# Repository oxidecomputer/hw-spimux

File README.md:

# hw-spimux

PMOD Quad SPI flash mux debug board
Breaks out the Gimletlet QSPI port to a MT25QU256ABA8E12 Flash memory IC.

# Model Change Notices
We use Model Change Notices (MCNs) to track rework made in between CAD updates 
andboard spins.
These are preserved in this repo for historical and reference reasons even
after the CAD has been updated.

# Status
The CAD represents what was built without the MCN(s) applied.

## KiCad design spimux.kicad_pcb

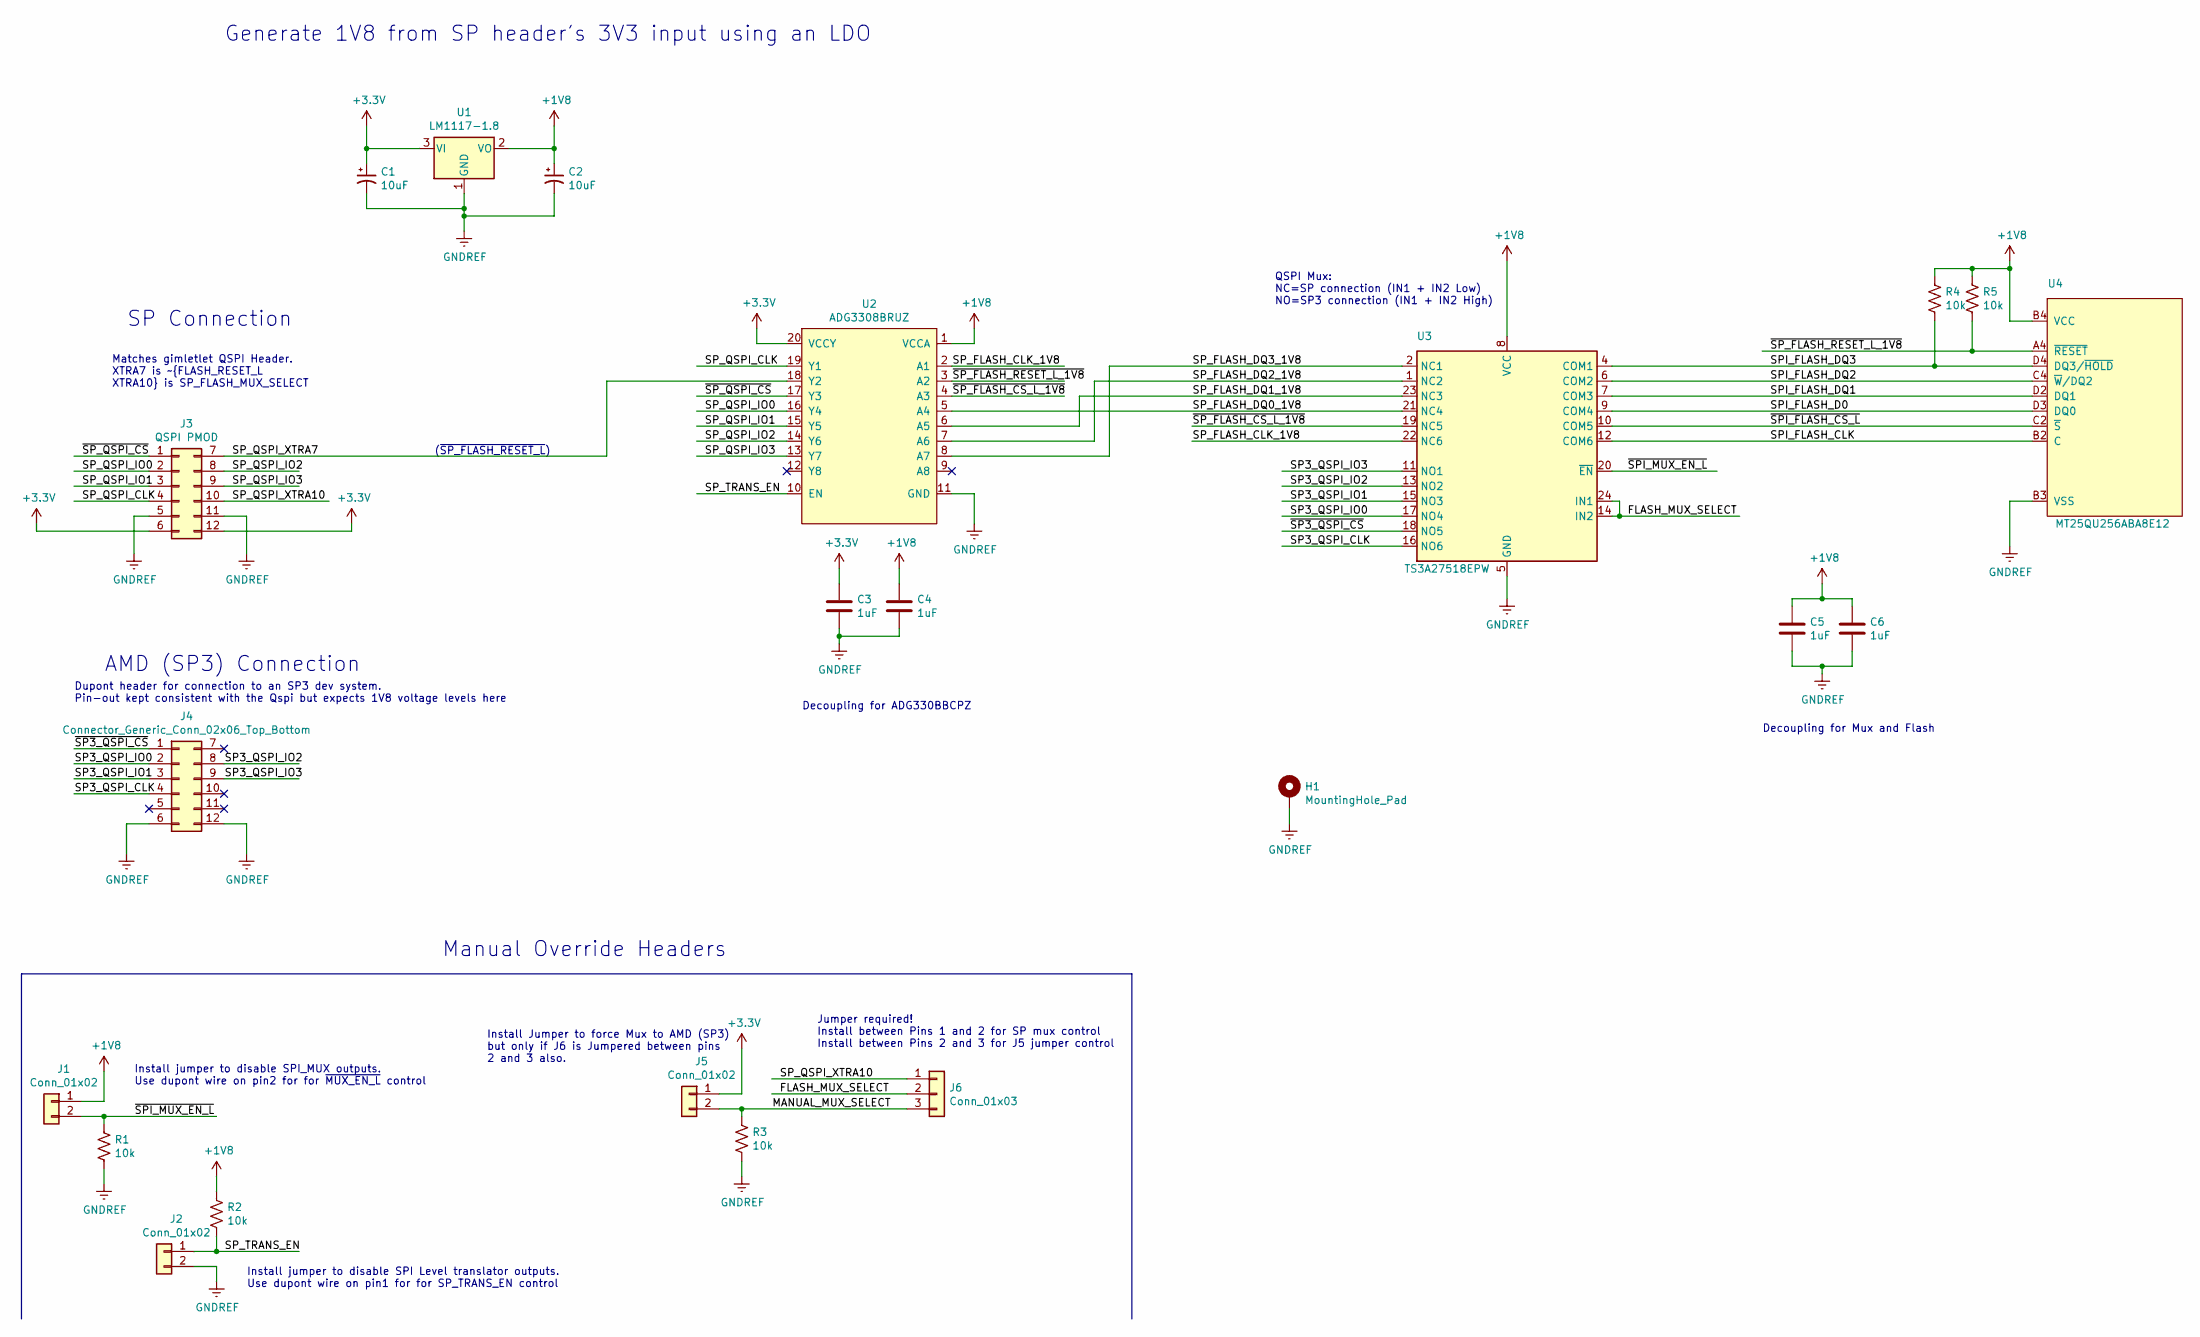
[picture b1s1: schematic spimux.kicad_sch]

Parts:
C1, C2: 10uF; CP_Elec_5x5.3; MPN EDK106M050A9DAA
C3, C4, C5, C6: 1uF; C_0402_1005Metric
H1: MountingHole_Pad; MountingHole_3.2mm_M3_Pad
J1, J2, J5: Conn_01x02; PinHeader_1x02_P2.54mm_Vertical; MPN PRPC024SAAN-RC
J3: QSPI PMOD; PMOD_12pin_peripheral_horizontal
J4: Connector_Generic_Conn_02x06_Top_Bottom; PinHeader_2x06_P2.54mm_Vertical
J6: Conn_01x03; PinHeader_1x03_P2.54mm_Vertical; MPN PRPC024SAAN-RC
R1, R2, R3, R4, R5: 10k; R_0402_1005Metric
U1: LM1117-1.8; SOT-223; MPN LM1117MPX-18NOPB
U2: ADG3308BRUZ; TSSOP-20_4.4x6.5mm_P0.65mm
U3: TS3A27518EPW; TSSOP-24_4.4x7.8mm_P0.65mm; MPN TS3A27518EPWR
U4: MT25QU256ABA8E12; BGA-25_5x5_6.0x8.0mm

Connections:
+1V8: C2.1, C4.1, C5.1, C6.1, J1.1, R2.1, R4.1, R5.1, U1.2 (VO), U2.1 (VCCA), U3.8 (VCC), U4.B4 (VCC)
+3V3: C1.1, C3.1, J3.6, J3.12, J5.1, U1.3 (VI), U2.20 (VCCY)
/FLASH_MUX_SELECT: J6.2, U3.14 (IN2), U3.24 (IN1)
/MANUAL_MUX_SELECT: J5.2, J6.3, R3.1
/SP3_QSPI_CLK: J4.4, U3.16 (NO6)
/SP3_QSPI_IO0: J4.2, U3.17 (NO4)
/SP3_QSPI_IO1: J4.3, U3.15 (NO3)
/SP3_QSPI_IO2: J4.8, U3.13 (NO2)
/SP3_QSPI_IO3: J4.9, U3.11 (NO1)
/SPI_FLASH_CLK: U3.12 (COM6), U4.B2 (C)
/SPI_FLASH_D0: U3.9 (COM4), U4.D3 (DQ0)
/SPI_FLASH_DQ1: U3.7 (COM3), U4.D2 (DQ1)
/SPI_FLASH_DQ2: U3.6 (COM2), U4.C4 (~W/DQ2)
/SPI_FLASH_DQ3: R4.2, U3.4 (COM1), U4.D4 (DQ3/~HOLD)
/SP_FLASH_CLK_1V8: U2.2 (A1), U3.22 (NC6)
/SP_FLASH_DQ0_1V8: U2.5 (A4), U3.21 (NC4)
/SP_FLASH_DQ1_1V8: U2.6 (A5), U3.23 (NC3)
/SP_FLASH_DQ2_1V8: U2.7 (A6), U3.1 (NC2)
/SP_FLASH_DQ3_1V8: U2.8 (A7), U3.2 (NC1)
/SP_QSPI_CLK: J3.4, U2.19 (Y1)
/SP_QSPI_IO0: J3.2, U2.16 (Y4)
/SP_QSPI_IO1: J3.3, U2.15 (Y5)
/SP_QSPI_IO2: J3.8, U2.14 (Y6)
/SP_QSPI_IO3: J3.9, U2.13 (Y7)
/SP_QSPI_XTRA7: J3.7, U2.18 (Y2)
/SP_QSPI_XTRA10: J3.10, J6.1
/SP_TRANS_EN: J2.1, R2.2, U2.10 (EN)
/~SP3_QSPI_CS: J4.1, U3.18 (NO5)
/~SPI_FLASH_CS_L: U3.10 (COM5), U4.C2 (~S)
/~SPI_MUX_EN_L: J1.2, R1.1, U3.20 (~EN)
/~SP_FLASH_CS_L_1V8: U2.4 (A3), U3.19 (NC5)
/~SP_FLASH_RESET_L_1V8: R5.2, U2.3 (A2), U4.A4 (~RESET)
/~SP_QSPI_CS: J3.1, U2.17 (Y3)
GNDREF: C1.2, C2.2, C3.2, C4.2, C5.2, C6.2, H1.1, J2.2, J3.5, J3.11, J4.6, J4.12, R1.2, R3.2, U1.1 (GND), U2.11 (GND), U3.5 (GND), U4.B3 (VSS)

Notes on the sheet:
(~{SP_FLASH_RESET_L})
Dupont header for connection to an SP3 dev system. Pin-out kept consistent with the Qspi but expects 1V8 voltage levels here
Matches gimletlet QSPI Header. XTRA7 is ~{FLASH_RESET_L XTRA10} is SP_FLASH_MUX_SELECT
Manual Override Headers
Jumper required! Install between Pins 1 and 2 for SP mux control Install between Pins 2 and 3 for J5 jumper control
QSPI Mux: NC=SP connection (IN1 + IN2 Low) NO=SP3 connection (IN1 + IN2 High)
Install jumper to disable SPI_MUX outputs. Use dupont wire on pin2 for for ~{MUX_EN_L} control
Install Jumper to force Mux to AMD (SP3) but only if J6 is Jumpered between pins 2 and 3 also.
SP Connection
Decoupling for Mux and Flash
AMD (SP3) Connection
Decoupling for ADG330BBCPZ
Install jumper to disable SPI Level translator outputs. Use dupont wire on pin1 for for SP_TRANS_EN control
Generate 1V8 from SP header's 3V3 input using an LDO

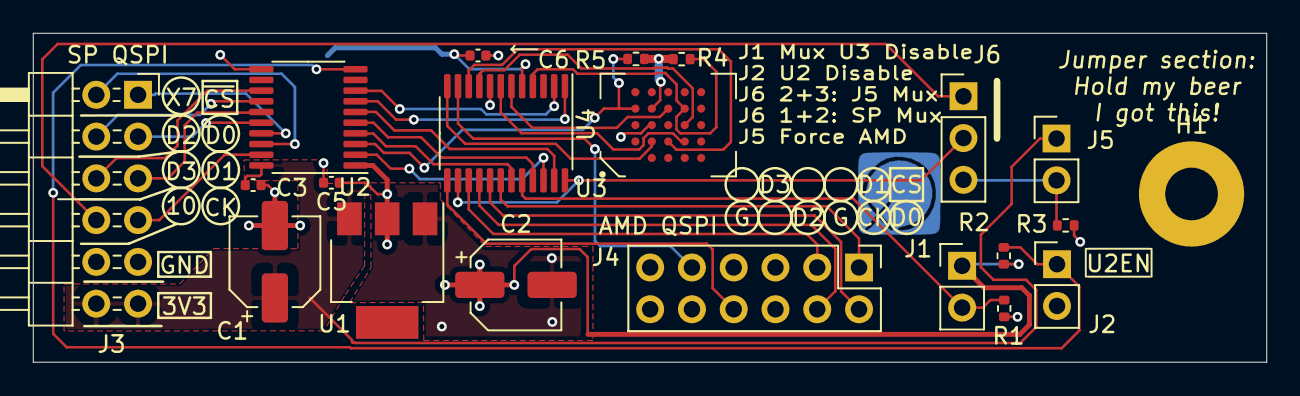
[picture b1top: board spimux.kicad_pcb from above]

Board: 2 copper layers, 75.0 x 20.0 mm, 22 parts (1 on the bottom side), 34 nets.

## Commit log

2023-02-24 Initial spi mux move to its own repo
2023-02-24 Add gitignore, remove backups folder
2023-02-24 Push badges
